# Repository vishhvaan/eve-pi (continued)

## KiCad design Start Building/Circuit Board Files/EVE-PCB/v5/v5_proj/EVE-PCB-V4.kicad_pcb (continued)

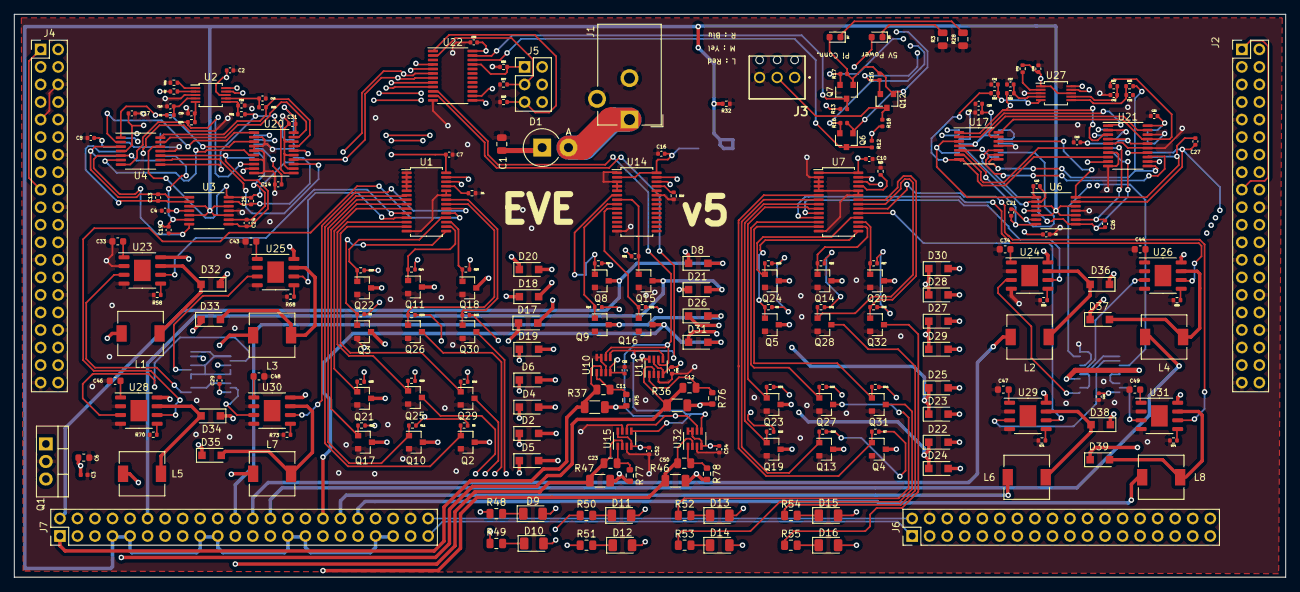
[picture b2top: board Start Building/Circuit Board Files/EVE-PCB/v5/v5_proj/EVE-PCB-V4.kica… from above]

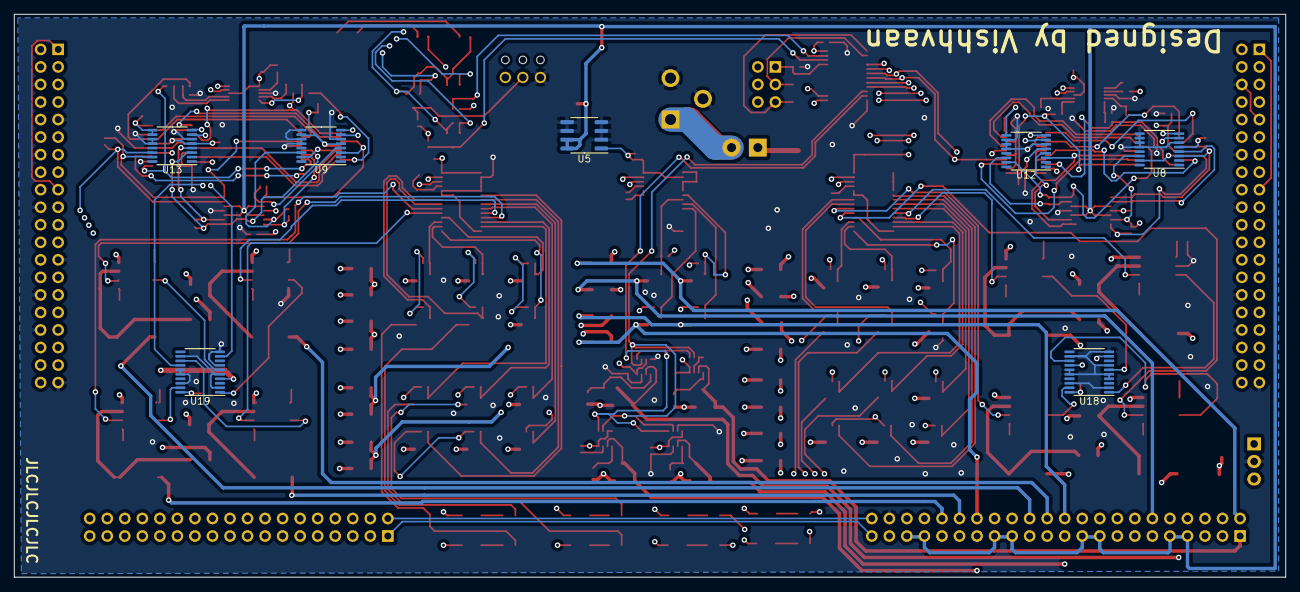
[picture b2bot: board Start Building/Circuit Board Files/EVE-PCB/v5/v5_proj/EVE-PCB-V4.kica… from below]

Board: 4 copper layers, 184.2 x 81.5 mm, 248 parts (7 on the bottom side), 193 nets.

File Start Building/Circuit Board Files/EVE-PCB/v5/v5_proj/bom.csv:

Comment,Designator,Footprint,LCSC
"10μF","C1","Capacitor_SMD:C_0805_2012Metric","C15850"
"1μF","C11,C12,C23,C50","Capacitor_SMD:C_0805_2012Metric","C28323"
"10pF","C13,C19,C20,C21,C24,C25,C26,C27","Capacitor_SMD:C_0402_1005Metric","C32949"
"2.2μF","C33,C34,C43,C44,C46,C47,C48,C49","Capacitor_SMD:C_0603_1608Metric","C23630"
"0.1μF","C2,C3,C4,C5,C7,C8,C9,C10,C14,C15,C16,C17,C18,C22,C28,C29,C30,C31,C32,C35,C36,C37,C38,C39,C40,C41,C42,C45,C51,C52,C54","Capacitor_SMD:C_0402_1005Metric","C1525"
"1μF","C6","Capacitor_SMD:C_0603_1608Metric","C5673"
"MUR480ERLG","D1","Diode_THT:D_DO-201AE_P3.81mm_Vertical_AnodeUp",""
"19-217/GHC-YR1S2/3T","D3","LED_SMD:LED_0603_1608Metric","C72043"
"PMEG6010CEH","D2,D4,D5,D6,D8,D17,D18,D19,D20,D21,D22,D23,D24,D25,D26,D27,D28,D29,D30,D31,D32,D33,D34,D35,D36,D37,D38,D39","Diode_SMD:D_SOD-123F","C110797"
"19-213/Y2C-CQ2R2L/3T","D7","LED_SMD:LED_0603_1608Metric","C72038"
"11-21/BHC-AQ2S1M/2T","D9,D10,D11,D12,D13,D14,D15,D16","LED_SMD:LED_1206_3216Metric","C264323"
"PJ-102AH","J1","Connector_BarrelJack:BarrelJack_CUI_PJ-102AH_Horizontal",""
"2x20 Male Header","J2,J4","Connector_PinHeader_2.54mm:PinHeader_2x20_P2.54mm_Vertical",""
"1725669","J3","1725669andothers:1725669",""
"Conn_02x03_Odd_Even","J5","Connector_PinHeader_2.54mm:PinHeader_2x03_P2.54mm_Vertical",""
"Conn_02x18_Odd_Even","J6","Connector_PinHeader_2.54mm:PinHeader_2x18_P2.54mm_Vertical",""
"Conn_02x22_Odd_Even","J7","Connector_PinHeader_2.54mm:PinHeader_2x22_P2.54mm_Vertical",""
"680uH","L1,L2,L3,L4,L5,L6,L7,L8","Inductor_SMD:L_6.3x6.3_H3","C168101"
"UA7805CKCT","Q1","Package_TO_SOT_THT:TO-220-3_Vertical",""
"DMN6140LQ-7","Q2,Q3,Q4,Q5,Q6,Q7,Q8,Q9,Q10,Q11,Q12,Q13,Q14,Q15,Q16,Q17,Q18,Q19,Q20,Q21,Q22,Q23,Q24,Q25,Q26,Q27,Q28,Q29,Q30,Q31,Q32","Package_TO_SOT_SMD:SOT-23","C155271"
"330KΩ","R1,R61,R62,R63,R64,R65,R66,R67","Resistor_SMD:R_0402_1005Metric","C25778"
"4.7KΩ","R15,R18","Resistor_SMD:R_0402_1005Metric","C25900"
"10KΩ","R2,R4,R5,R6,R7,R8,R9,R10,R11,R12,R13,R14,R16,R17,R19,R20,R21,R22,R23,R24,R25,R26,R27,R29,R30,R31,R32,R33,R34,R35,R38,R39,R40,R41,R42,R43,R44,R45,R56,R57,R60,R72","Resistor_SMD:R_0402_1005Metric","C25744"
"80Ω","R28,R48,R49,R50,R51,R52,R53,R54,R55","Resistor_SMD:R_0805_2012Metric","C17833"
"169Ω","R3","Resistor_SMD:R_0805_2012Metric","C17489"
"2.15Ω","R36,R37,R46,R47","Resistor_SMD:R_1206_3216Metric","C247507"
"20KΩ","R58,R59,R68,R69,R70,R71,R73,R74","Resistor_SMD:R_0402_1005Metric","C25765"
"750KΩ","R75,R76,R77,R78","Resistor_SMD:R_0603_1608Metric","C23240"
"PCA9685PW","U1,U7,U14","Package_SO:TSSOP-28_4.4x9.7mm_P0.65mm","C92206"
"INA219AxDCN","U10,U11,U15,U32","Package_TO_SOT_SMD:SOT-23-8","C87469"
"AD5254 - 50K","U18,U19,U20,U21","Package_SO:TSSOP-20_4.4x6.5mm_P0.65mm",""
"TCA9548APWR","U22","Package_SO:TSSOP-24_4.4x7.8mm_P0.65mm",""
"TPS92511DDAR","U23,U24,U25,U26,U28,U29,U30,U31","Package_SO:HSOP-8-1EP_3.9x4.9mm_P1.27mm_EP2.41x3.1mm","C206179"
"ADS1115IDGSR","U2,U27","Package_SO:MSOP-10_3x3mm_P0.5mm","C37593"
"TLV4314IPWR","U3,U4,U6,U17","Package_SO:TSSOP-14_4.4x5mm_P0.65mm","C106874"
"MCP1501-10E/SN","U5","Package_SO:SOIC-8_3.9x4.9mm_P1.27mm",""
"AD5242","U8,U9,U12,U13","Package_SO:TSSOP-16_4.4x5mm_P0.65mm",""

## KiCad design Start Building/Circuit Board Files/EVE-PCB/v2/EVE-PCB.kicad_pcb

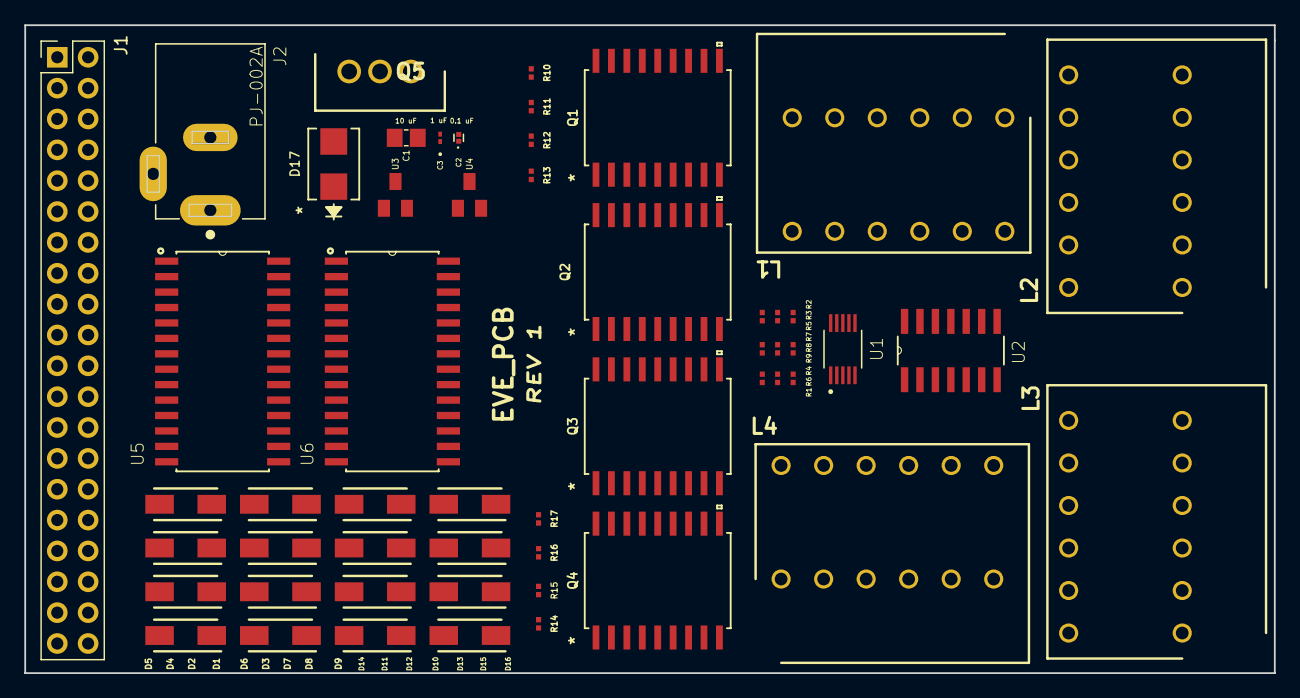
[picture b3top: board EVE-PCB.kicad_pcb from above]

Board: 2 copper layers, 102.9 x 53.3 mm, 54 parts (0 on the bottom side), 70 nets, no tracks yet.

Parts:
C1: 10 uF; CAPC2012X135N
C2: 0.1 uF; CAPC0603X39N
C3: 1 uF; GRM033R71E102KA01D
D1, D2, D3, D4, D5, D6, D7, D8, D9, D10, D11, D12, D13, D14, D15, D16: BAT43; B160-13-F
D17: S1KB; S1KB-13-F
J1: Raspberry_Pi_2_3; PinHeader_2x20_P2.54mm_Vertical
J2: PJ-002A; CUI_PJ-002A
L1, L2, L3, L4: SHDR12W60P935X350_2X6_2250X1800X2420P; 1841539
Q1, Q2, Q3, Q4: DW18; ULN2803ADWR
Q5: TO254P465X1016X1883-3P; UA7805CKCT
R1, R2, R3, R4: 1M; RC0201FR-071ML
R5, R6, R7, R8, R9: 10K; RC0201FR-0710KL
R10, R12, R14, R16: 130; RC0201FR-07130RL
R11, R13, R15, R17: 400; RC0201FR-07402RL
U1: ADS1015IDGSR; SOP50P490X110-10N
U2: LM324DR; SOIC127P600X175-14N
U3, U4: BSN20BKR; BSN20_215
U5, U6: MCP23017T-E_SO; SOIC127P1030X265-28N

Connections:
+3V3: J1.1, J1.17, R5.1, R9.1, U3.1, U4.1
+5V: C2.1, C3.1, Q5.3, R6.2, R7.1, R8.2, U1.8, U2.4, U5.9, U5.18, U6.9, U6.18
+12V: C1.1, D1.1, D2.1, D3.1, D4.1, D5.1, D6.1, D7.1, D8.1, D9.1, D10.1, D11.1, D12.1, D13.1, D14.1, D15.1, D16.1, D17.1, L1.7, L1.8, L1.9, L1.10, L1.11, L2.7, L2.8, L2.9, L2.10, L2.11, L3.7, L3.8, L3.9, L3.10, L3.11, L4.7, L4.8, L4.9, L4.10, L4.11, Q1.10, Q2.10, Q3.10, Q4.10, Q5.1
/AIN0: R1.1, U1.4, U2.1
/AIN1: R2.1, U1.5, U2.7
/AIN2: R3.1, U1.6, U2.8
/AIN3: R4.1, U1.7, U2.14
/DAC1/A_DRUGS1: D1.2, L1.1, Q1.18
/DAC1/A_DRUGS2: D5.2, L2.1, Q2.18
/DAC1/A_FAN1: Q1.14, R11.1
/DAC1/A_FAN2: Q2.14, R13.1
/DAC1/A_LED1: Q1.15, R10.1
/DAC1/A_LED2: Q2.15, R12.1
/DAC1/A_MEDIA1: D2.2, L1.2, Q1.17
/DAC1/A_MEDIA2: D6.2, L2.2, Q2.17
/DAC1/A_SFAN1: D4.2, L1.4, Q1.13, R11.2
/DAC1/A_SFAN2: D8.2, L2.4, Q2.13, R13.2
/DAC1/A_WASTE1: D3.2, L1.3, Q1.16
/DAC1/A_WASTE2: D7.2, L2.3, Q2.16
/DAC1/D_DRUGS1: Q1.1, U5.21
/DAC1/D_DRUGS2: Q2.1, U5.1
/DAC1/D_FAN1: Q1.5, U5.25
/DAC1/D_FAN2: Q2.5, U5.5
/DAC1/D_LED1: Q1.4, U5.24
/DAC1/D_LED2: Q2.4, U5.4
/DAC1/D_MEDIA1: Q1.2, U5.22
/DAC1/D_MEDIA2: Q2.2, U5.2
/DAC1/D_SFAN1: Q1.6, U5.26
/DAC1/D_SFAN2: Q2.6, U5.6
/DAC1/D_WASTE1: Q1.3, U5.23
/DAC1/D_WASTE2: Q2.3, U5.3
/DAC1/LED1_NEG: L1.5, R10.2
/DAC1/LED2_NEG: L2.5, R12.2
/DAC2/A_DRUGS3: D9.2, L3.1, Q3.18
/DAC2/A_DRUGS4: D13.2, L4.1, Q4.18
/DAC2/A_FAN3: Q3.14, R15.1
/DAC2/A_FAN4: Q4.14, R17.1
/DAC2/A_LED3: Q3.15, R14.1
/DAC2/A_LED4: Q4.15, R16.1
/DAC2/A_MEDIA3: D10.2, L3.2, Q3.17
/DAC2/A_MEDIA4: D14.2, L4.2, Q4.17
/DAC2/A_SFAN3: D12.2, L3.4, Q3.13, R15.2
/DAC2/A_SFAN4: D16.2, L4.4, Q4.13, R17.2
/DAC2/A_WASTE3: D11.2, L3.3, Q3.16
/DAC2/A_WASTE4: D15.2, L4.3, Q4.16
/DAC2/D_DRUGS3: Q3.1, U6.21
/DAC2/D_DRUGS4: Q4.1, U6.1
/DAC2/D_FAN3: Q3.5, U6.25
/DAC2/D_FAN4: Q4.5, U6.5
/DAC2/D_LED3: Q3.4, U6.24
/DAC2/D_LED4: Q4.4, U6.4
/DAC2/D_MEDIA3: Q3.2, U6.22
/DAC2/D_MEDIA4: Q4.2, U6.2
/DAC2/D_SFAN3: Q3.6, U6.26
/DAC2/D_SFAN4: Q4.6, U6.6
/DAC2/D_WASTE3: Q3.3, U6.23
/DAC2/D_WASTE4: Q4.3, U6.3
/DAC2/LED3_NEG: L3.5, R14.2
/DAC2/LED4_NEG: L4.5, R16.2
/PD1_NEG: L1.6, R1.2, U2.2
/PD2_NEG: L2.6, R2.2, U2.6
/PD3_NEG: L3.6, R3.2, U2.9
/PD4_NEG: L4.6, R4.2, U2.13
/SCL: R6.1, U1.10, U3.3, U5.12, U6.12
/SCL-3.3: J1.5, R5.2, U3.2
/SDA: R8.1, U1.9, U4.3, U5.13, U6.13
/SDA-3.3: J1.3, R9.2, U4.2
GND: C1.2, C2.2, C3.2, J1.6, J1.9, J1.14, J1.20, J1.25, J1.30, J1.34, J1.39, J2.2, J2.3, L1.12, L2.12, L3.12, L4.12, Q1.9, Q2.9, Q3.9, Q4.9, Q5.2, U1.1, U1.3, U2.3, U2.5, U2.10, U2.11, U2.12, U5.10, U5.15, U5.16, U5.17, U6.10, U6.15, U6.16, U6.17
unnamed: D17.2, J2.1
unnamed: R7.2, U1.2

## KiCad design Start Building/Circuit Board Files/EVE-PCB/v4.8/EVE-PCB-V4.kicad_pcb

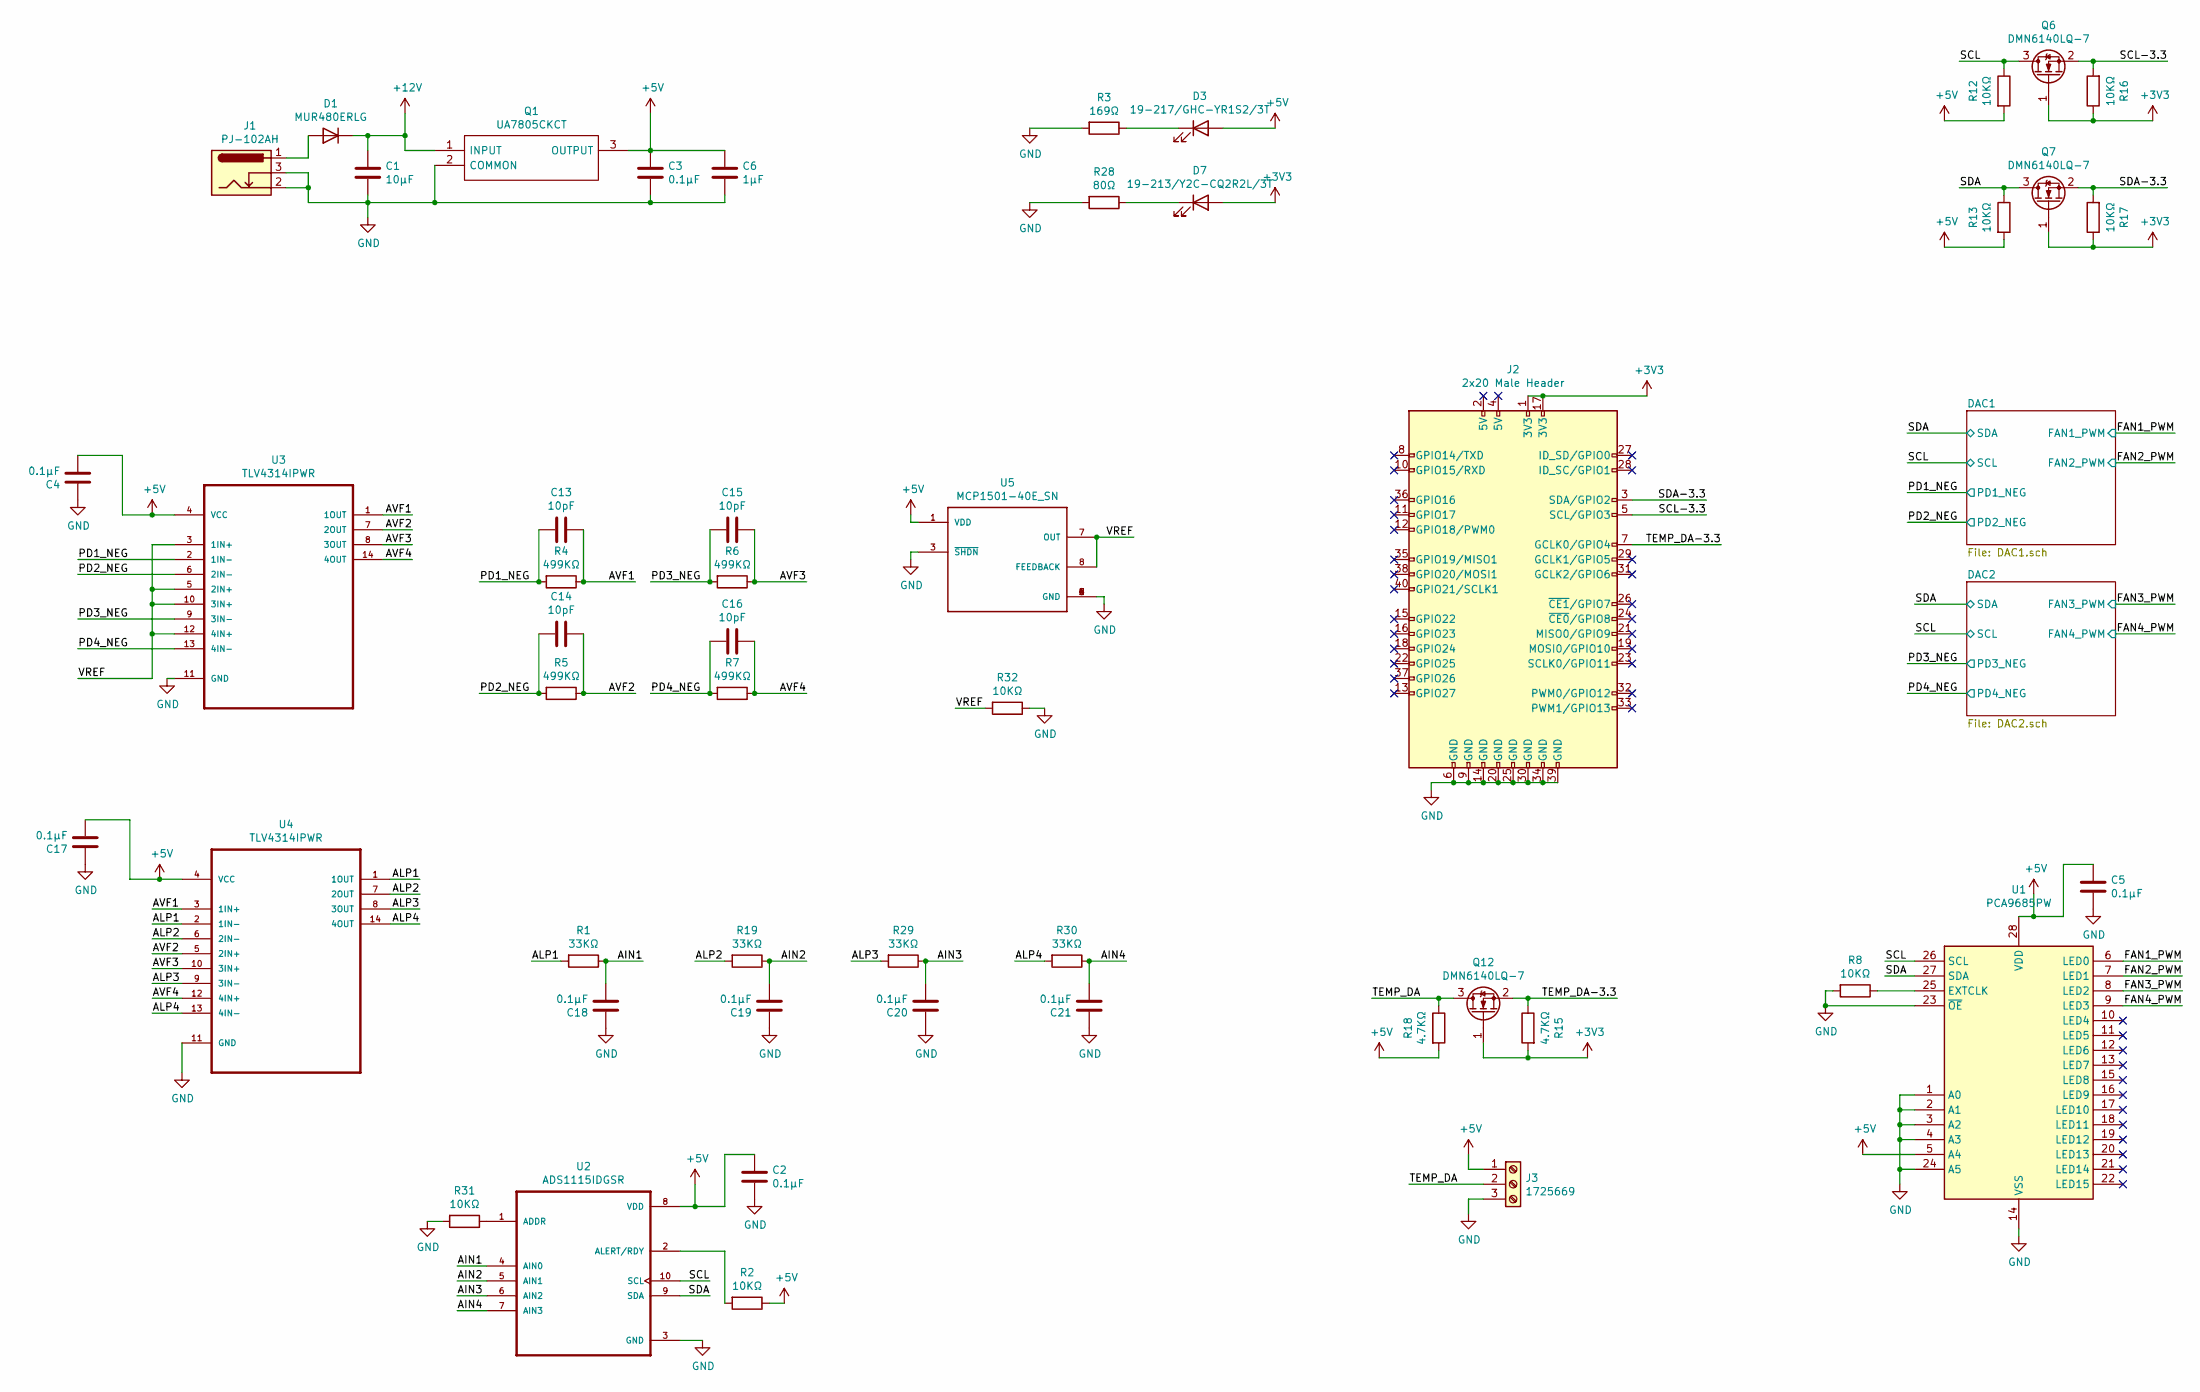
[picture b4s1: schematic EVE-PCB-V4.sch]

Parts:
C1: 10μF; C_0805_2012Metric; LCSC C15850
C2, C3, C4, C5, C17, C18, C19, C20, C21: 0.1μF; C_0402_1005Metric; LCSC C1525
C6: 1μF; C_0603_1608Metric; LCSC C5673
C13, C14, C15, C16: 10pF; C_0402_1005Metric; LCSC C32949
D1: MUR480ERLG; D_DO-201AE_P3.81mm_Vertical_AnodeUp
D3: 19-217/GHC-YR1S2/3T; LED_0603_1608Metric; LCSC C72043
D7: 19-213/Y2C-CQ2R2L/3T; LED_0603_1608Metric; LCSC C72038
J1: PJ-102AH; BarrelJack_CUI_PJ-102AH_Horizontal
J2: 2x20 Male Header; PinHeader_2x20_P2.54mm_Vertical
J3: 1725669
Q1: UA7805CKCT; TO-220-3_Vertical; Mouser Part Number 595-UA7805CKCT
Q6, Q7, Q12: DMN6140LQ-7; SOT-23; LCSC C155271
R1, R19, R29, R30: 33KΩ; R_0402_1005Metric; LCSC C25779
R2, R8, R12, R13, R16, R17, R31, R32: 10KΩ; R_0402_1005Metric; LCSC C25744
R3: 169Ω; R_0805_2012Metric; LCSC C17489
R4, R5, R6, R7: 499KΩ; R_0402_1005Metric; LCSC C25793
R15, R18: 4.7KΩ; R_0402_1005Metric; LCSC C25900
R28: 80Ω; R_0805_2012Metric; LCSC C17833
U1: PCA9685PW; TSSOP-28_4.4x9.7mm_P0.65mm; LCSC C92206
U2: ADS1115IDGSR; MSOP-10_3x3mm_P0.5mm; LCSC C37593
U3, U4: TLV4314IPWR; TSSOP-14_4.4x5mm_P0.65mm; LCSC C106874
U5: MCP1501-40E_SN; SOIC-8_3.9x4.9mm_P1.27mm

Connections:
+3V3: D7.2 (A), J2.1 (3V3), J2.17 (3V3), Q6.1 (G), Q7.1 (G), Q12.1 (G), R15.2, R16.1, R17.1
+5V: C2.1, C3.1, C4.2, C5.1, C6.1, C17.2, D3.2 (A), J3.1, Q1.3 (OUTPUT), R2.1, R12.2, R13.2, R18.2, U1.5 (A4), U1.28 (VDD), U2.8 (VDD), U3.4 (VCC), U4.4 (VCC), U5.1 (VDD); also elsewhere on the board
+12V: C1.1, D1.1 (K), Q1.1 (INPUT); also elsewhere on the board
/AIN1: C18.2, R1.1, U2.4 (AIN0)
/AIN2: C19.2, R19.1, U2.5 (AIN1)
/AIN3: C20.2, R29.1, U2.6 (AIN2)
/AIN4: C21.2, R30.1, U2.7 (AIN3)
/ALP1: R1.2, U4.1 (1OUT), U4.2 (1IN-)
/ALP2: R19.2, U4.6 (2IN-), U4.7 (2OUT)
/ALP3: R29.2, U4.8 (3OUT), U4.9 (3IN-)
/ALP4: R30.2, U4.13 (4IN-), U4.14 (4OUT)
/AVF1: C13.1, R4.1, U3.1 (1OUT), U4.3 (1IN+)
/AVF2: C14.1, R5.1, U3.7 (2OUT), U4.5 (2IN+)
/AVF3: C15.1, R6.1, U3.8 (3OUT), U4.10 (3IN+)
/AVF4: C16.1, R7.1, U3.14 (4OUT), U4.12 (4IN+)
/FAN1_PWM: U1.6 (LED0); also elsewhere on the board
/FAN2_PWM: U1.7 (LED1); also elsewhere on the board
/FAN3_PWM: U1.8 (LED2); also elsewhere on the board
/FAN4_PWM: U1.9 (LED3); also elsewhere on the board
/PD1_NEG: C13.2, R4.2, U3.2 (1IN-); also elsewhere on the board
/PD2_NEG: C14.2, R5.2, U3.6 (2IN-); also elsewhere on the board
/PD3_NEG: C15.2, R6.2, U3.9 (3IN-); also elsewhere on the board
/PD4_NEG: C16.2, R7.2, U3.13 (4IN-); also elsewhere on the board
/SCL: Q6.3 (D), R12.1, U1.26 (SCL), U2.10 (SCL); also elsewhere on the board
/SCL-3.3: J2.5 (SCL/GPIO3), Q6.2 (S), R16.2
/SDA: Q7.3 (D), R13.1, U1.27 (SDA), U2.9 (SDA); also elsewhere on the board
/SDA-3.3: J2.3 (SDA/GPIO2), Q7.2 (S), R17.2
/TEMP_DA: J3.2, Q12.3 (D), R18.1
/TEMP_DA-3.3: J2.7 (GCLK0/GPIO4), Q12.2 (S), R15.1
/VREF: R32.2, U3.3 (1IN+), U3.5 (2IN+), U3.10 (3IN+), U3.12 (4IN+), U5.7 (OUT), U5.8 (FEEDBACK)
GND: C1.2, C2.2, C3.2, C4.1, C5.2, C6.2, C17.1, C18.1, C19.1, C20.1, C21.1, J1.2, J1.3, J2.6 (GND), J2.9 (GND), J2.14 (GND), J2.20 (GND), J2.25 (GND), J2.30 (GND), J2.34 (GND), J2.39 (GND), J3.3, Q1.2 (COMMON), R3.2, R8.2, R28.2, R31.2, R32.1, U1.1 (A0), U1.2 (A1), U1.3 (A2), U1.4 (A3), U1.14 (VSS), U1.23 (~OE), U1.24 (A5), U2.3 (GND), U3.11 (GND), U4.11 (GND), U5.2 (GND), U5.3 (~SHDN~), U5.4 (GND), U5.5 (GND), U5.6 (GND); also elsewhere on the board
unnamed: D1.2 (A), J1.1
unnamed: D3.1 (K), R3.1
unnamed: D7.1 (K), R28.1
unnamed: R2.2, U2.2 (ALERT/RDY)
unnamed: R8.1, U1.25 (EXTCLK)
unnamed: R31.1, U2.1 (ADDR)

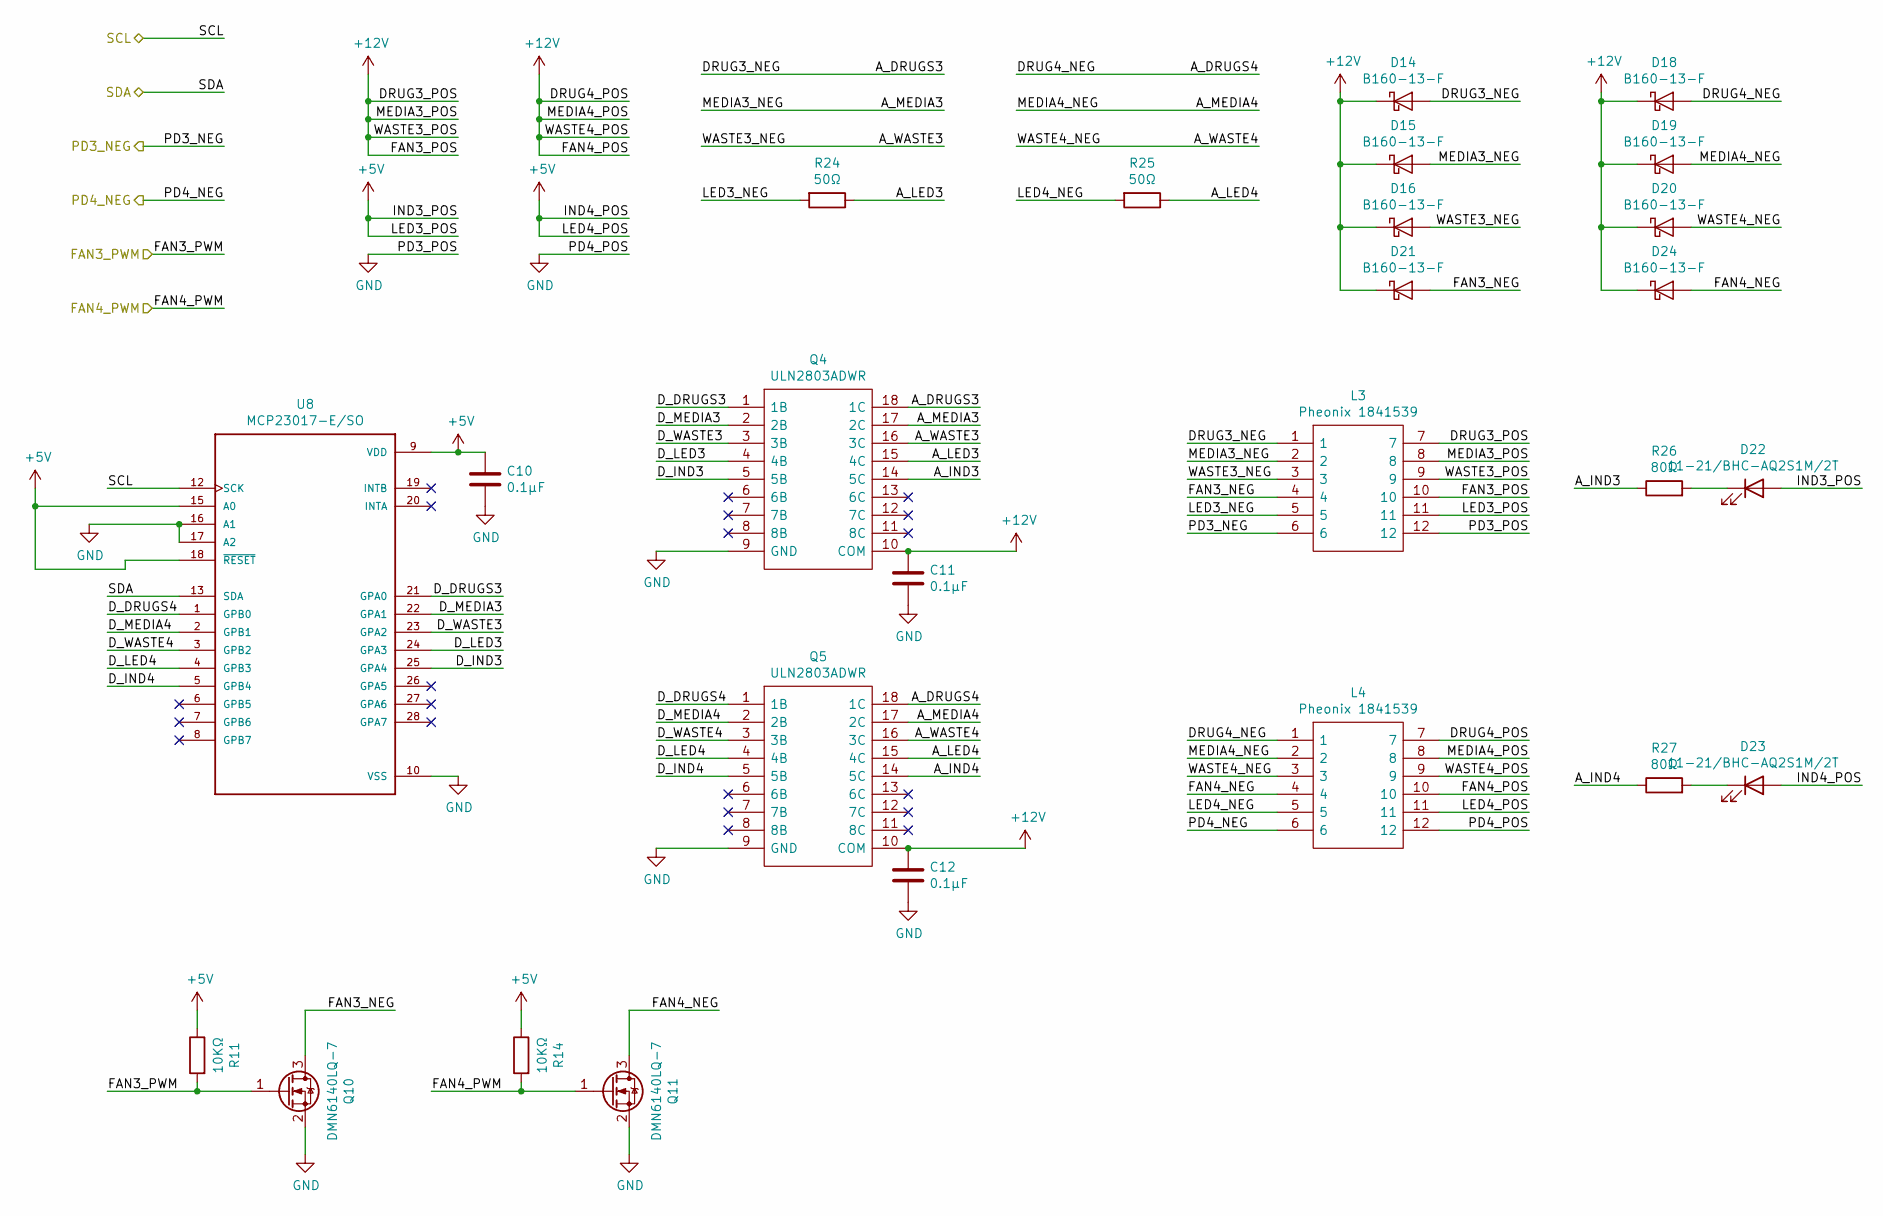
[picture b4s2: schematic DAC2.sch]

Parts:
C10, C11, C12: 0.1μF; C_0402_1005Metric; LCSC C1525
D14, D15, D16, D18, D19, D20, D21, D24: B160-13-F; D_SMA; LCSC C24784
D22, D23: 11-21/BHC-AQ2S1M/2T; LED_1206_3216Metric; LCSC C264323
L3, L4: Pheonix 1841539; 1841539; Mouser Part Number 651-1841539
Q4, Q5: ULN2803ADWR; SOIC-18W_7.5x11.6mm_P1.27mm; Mouser Part Number 595-ULN2803ADWR
Q10, Q11: DMN6140LQ-7; SOT-23; LCSC C155271
R11, R14: 10KΩ; R_0402_1005Metric; LCSC C25744
R24, R25: 50Ω; R_2512_6332Metric; LCSC C25487
R26, R27: 80Ω; R_0805_2012Metric; LCSC C17833
U8: MCP23017-E/SO; SOIC-28W_7.5x17.9mm_P1.27mm; LCSC C47023

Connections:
+5V: C10.1, D22.2 (A), D23.2 (A), L3.11, L4.11, R11.1, R14.1, U8.9 (VDD), U8.15 (A0), U8.18 (~RESET~); also elsewhere on the board
+12V: C11.1, C12.1, D14.1 (K), D15.1 (K), D16.1 (K), D18.1 (K), D19.1 (K), D20.1 (K), D21.1 (K), D24.1 (K), L3.7, L3.8, L3.9, L3.10, L4.7, L4.8, L4.9, L4.10, Q4.10 (COM), Q5.10 (COM); also elsewhere on the board
/DAC2/A_DRUGS3: D14.2 (A), L3.1, Q4.18 (1C)
/DAC2/A_DRUGS4: D18.2 (A), L4.1, Q5.18 (1C)
/DAC2/A_IND3: Q4.14 (5C), R26.1
/DAC2/A_IND4: Q5.14 (5C), R27.1
/DAC2/A_LED3: Q4.15 (4C), R24.1
/DAC2/A_LED4: Q5.15 (4C), R25.1
/DAC2/A_MEDIA3: D15.2 (A), L3.2, Q4.17 (2C)
/DAC2/A_MEDIA4: D19.2 (A), L4.2, Q5.17 (2C)
/DAC2/A_WASTE3: D16.2 (A), L3.3, Q4.16 (3C)
/DAC2/A_WASTE4: D20.2 (A), L4.3, Q5.16 (3C)
/DAC2/D_DRUGS3: Q4.1 (1B), U8.21 (GPA0)
/DAC2/D_DRUGS4: Q5.1 (1B), U8.1 (GPB0)
/DAC2/D_IND3: Q4.5 (5B), U8.25 (GPA4)
/DAC2/D_IND4: Q5.5 (5B), U8.5 (GPB4)
/DAC2/D_LED3: Q4.4 (4B), U8.24 (GPA3)
/DAC2/D_LED4: Q5.4 (4B), U8.4 (GPB3)
/DAC2/D_MEDIA3: Q4.2 (2B), U8.22 (GPA1)
/DAC2/D_MEDIA4: Q5.2 (2B), U8.2 (GPB1)
/DAC2/D_WASTE3: Q4.3 (3B), U8.23 (GPA2)
/DAC2/D_WASTE4: Q5.3 (3B), U8.3 (GPB2)
/DAC2/FAN3_NEG: D21.2 (A), L3.4, Q10.3 (D)
/DAC2/FAN4_NEG: D24.2 (A), L4.4, Q11.3 (D)
/DAC2/LED3_NEG: L3.5, R24.2
/DAC2/LED4_NEG: L4.5, R25.2
/FAN3_PWM: Q10.1 (G), R11.2; also elsewhere on the board
/FAN4_PWM: Q11.1 (G), R14.2; also elsewhere on the board
/PD3_NEG: L3.6; also elsewhere on the board
/PD4_NEG: L4.6; also elsewhere on the board
/SCL: U8.12 (SCK); also elsewhere on the board
/SDA: U8.13 (SDA); also elsewhere on the board
GND: C10.2, C11.2, C12.2, L3.12, L4.12, Q4.9 (GND), Q5.9 (GND), Q10.2 (S), Q11.2 (S), U8.10 (VSS), U8.16 (A1), U8.17 (A2); also elsewhere on the board
unnamed: D22.1 (K), R26.2
unnamed: D23.1 (K), R27.2

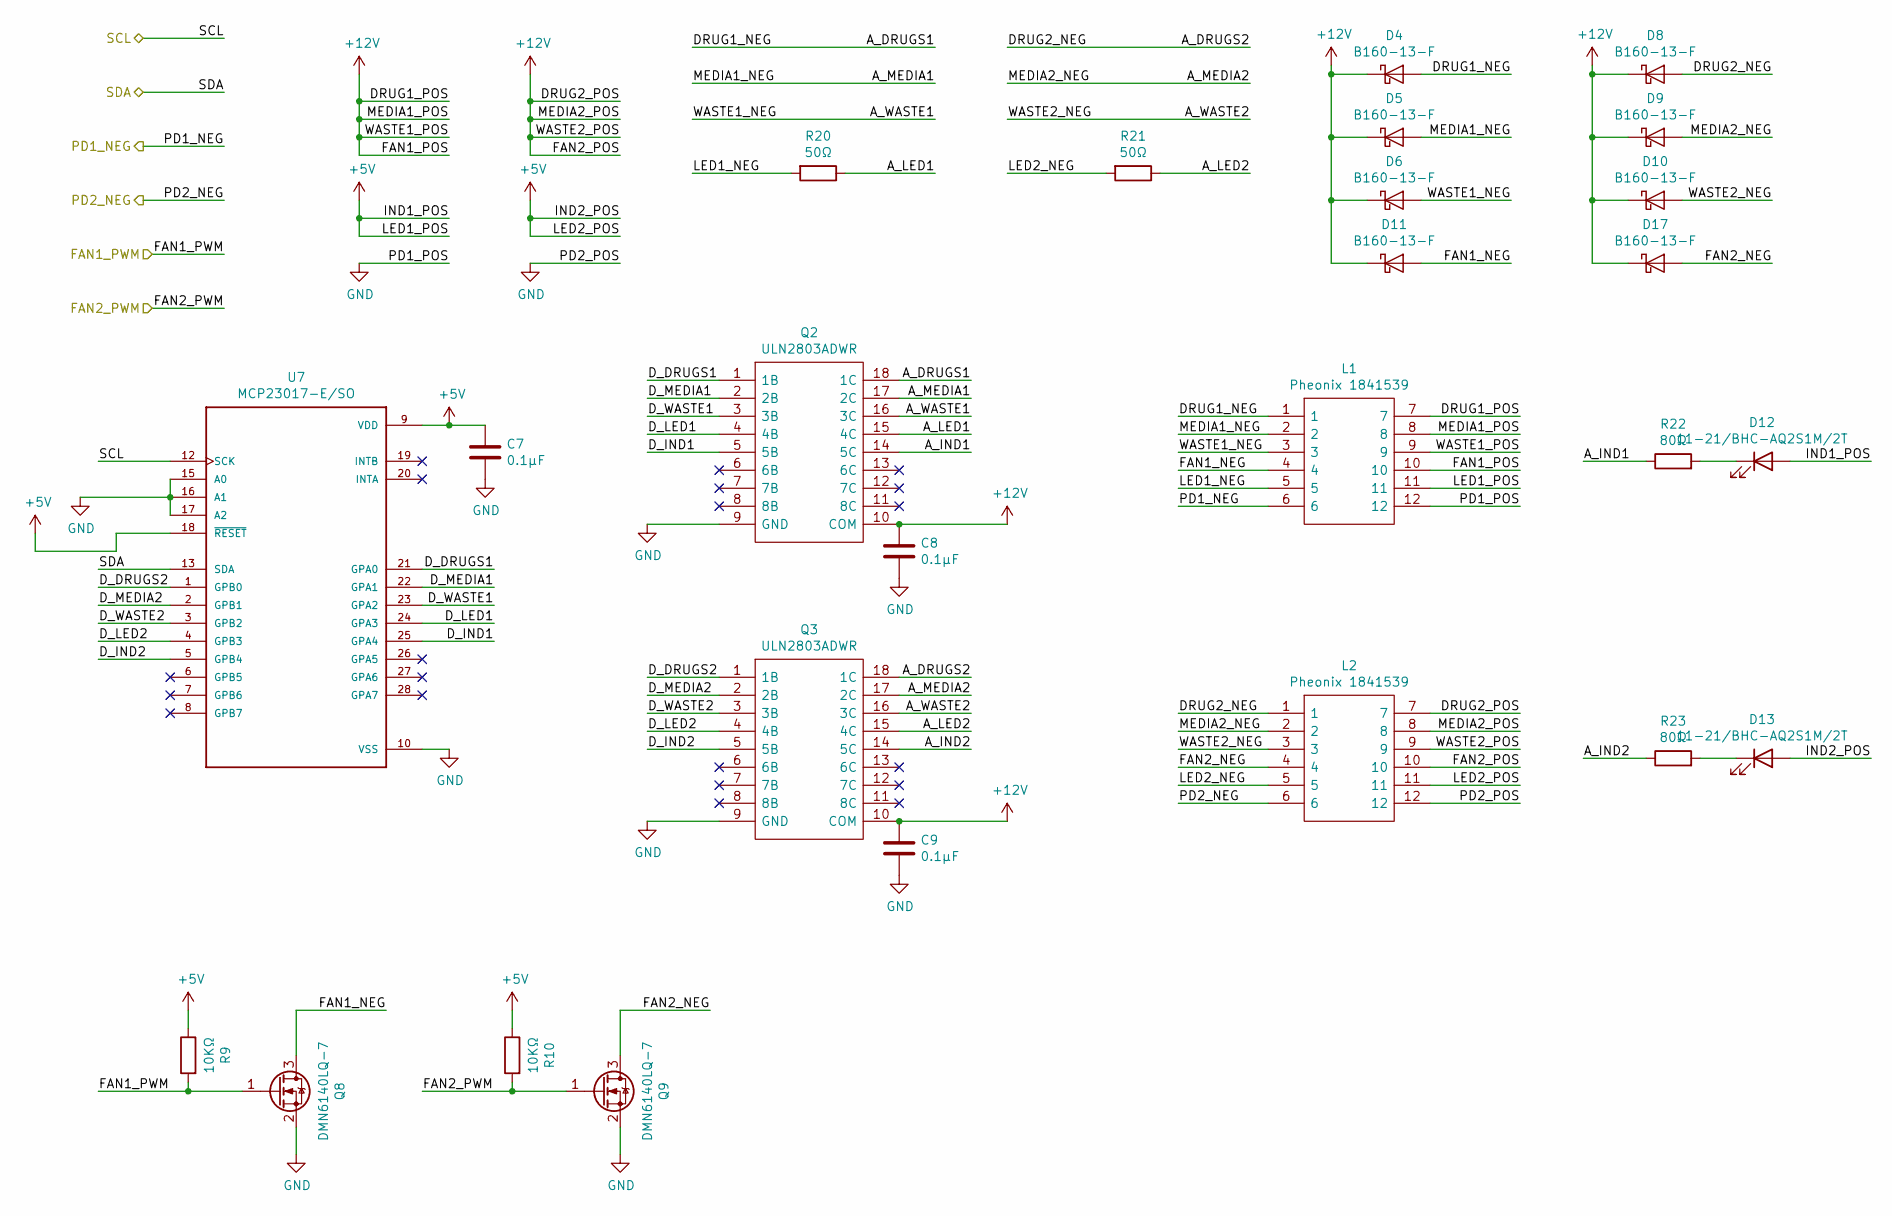
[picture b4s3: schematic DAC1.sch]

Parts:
C7, C8, C9: 0.1μF; C_0402_1005Metric; LCSC C1525
D4, D5, D6, D8, D9, D10, D11, D17: B160-13-F; D_SMA; LCSC C24784
D12, D13: 11-21/BHC-AQ2S1M/2T; LED_1206_3216Metric; LCSC C264323
L1, L2: Pheonix 1841539; 1841539; Mouser Part Number 651-1841539
Q2, Q3: ULN2803ADWR; SOIC-18W_7.5x11.6mm_P1.27mm; Mouser Part Number 595-ULN2803ADWR
Q8, Q9: DMN6140LQ-7; SOT-23; LCSC C155271
R9, R10: 10KΩ; R_0402_1005Metric; LCSC C25744
R20, R21: 50Ω; R_2512_6332Metric; LCSC C25487
R22, R23: 80Ω; R_0805_2012Metric; LCSC C17833
U7: MCP23017-E/SO; SOIC-28W_7.5x17.9mm_P1.27mm; LCSC C47023

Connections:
+5V: C7.1, D12.2 (A), D13.2 (A), L1.11, L2.11, R9.1, R10.1, U7.9 (VDD), U7.18 (~RESET~); also elsewhere on the board
+12V: C8.1, C9.1, D4.1 (K), D5.1 (K), D6.1 (K), D8.1 (K), D9.1 (K), D10.1 (K), D11.1 (K), D17.1 (K), L1.7, L1.8, L1.9, L1.10, L2.7, L2.8, L2.9, L2.10, Q2.10 (COM), Q3.10 (COM); also elsewhere on the board
/DAC1/A_DRUGS1: D4.2 (A), L1.1, Q2.18 (1C)
/DAC1/A_DRUGS2: D8.2 (A), L2.1, Q3.18 (1C)
/DAC1/A_IND1: Q2.14 (5C), R22.1
/DAC1/A_IND2: Q3.14 (5C), R23.1
/DAC1/A_LED1: Q2.15 (4C), R20.1
/DAC1/A_LED2: Q3.15 (4C), R21.1
/DAC1/A_MEDIA1: D5.2 (A), L1.2, Q2.17 (2C)
/DAC1/A_MEDIA2: D9.2 (A), L2.2, Q3.17 (2C)
/DAC1/A_WASTE1: D6.2 (A), L1.3, Q2.16 (3C)
/DAC1/A_WASTE2: D10.2 (A), L2.3, Q3.16 (3C)
/DAC1/D_DRUGS1: Q2.1 (1B), U7.21 (GPA0)
/DAC1/D_DRUGS2: Q3.1 (1B), U7.1 (GPB0)
/DAC1/D_IND1: Q2.5 (5B), U7.25 (GPA4)
/DAC1/D_IND2: Q3.5 (5B), U7.5 (GPB4)
/DAC1/D_LED1: Q2.4 (4B), U7.24 (GPA3)
/DAC1/D_LED2: Q3.4 (4B), U7.4 (GPB3)
/DAC1/D_MEDIA1: Q2.2 (2B), U7.22 (GPA1)
/DAC1/D_MEDIA2: Q3.2 (2B), U7.2 (GPB1)
/DAC1/D_WASTE1: Q2.3 (3B), U7.23 (GPA2)
/DAC1/D_WASTE2: Q3.3 (3B), U7.3 (GPB2)
/DAC1/FAN1_NEG: D11.2 (A), L1.4, Q8.3 (D)
/DAC1/FAN2_NEG: D17.2 (A), L2.4, Q9.3 (D)
/DAC1/LED1_NEG: L1.5, R20.2
/DAC1/LED2_NEG: L2.5, R21.2
/FAN1_PWM: Q8.1 (G), R9.2; also elsewhere on the board
/FAN2_PWM: Q9.1 (G), R10.2; also elsewhere on the board
/PD1_NEG: L1.6; also elsewhere on the board
/PD2_NEG: L2.6; also elsewhere on the board
/SCL: U7.12 (SCK); also elsewhere on the board
/SDA: U7.13 (SDA); also elsewhere on the board
GND: C7.2, C8.2, C9.2, L1.12, L2.12, Q2.9 (GND), Q3.9 (GND), Q8.2 (S), Q9.2 (S), U7.10 (VSS), U7.15 (A0), U7.16 (A1), U7.17 (A2); also elsewhere on the board
unnamed: D12.1 (K), R22.2
unnamed: D13.1 (K), R23.2

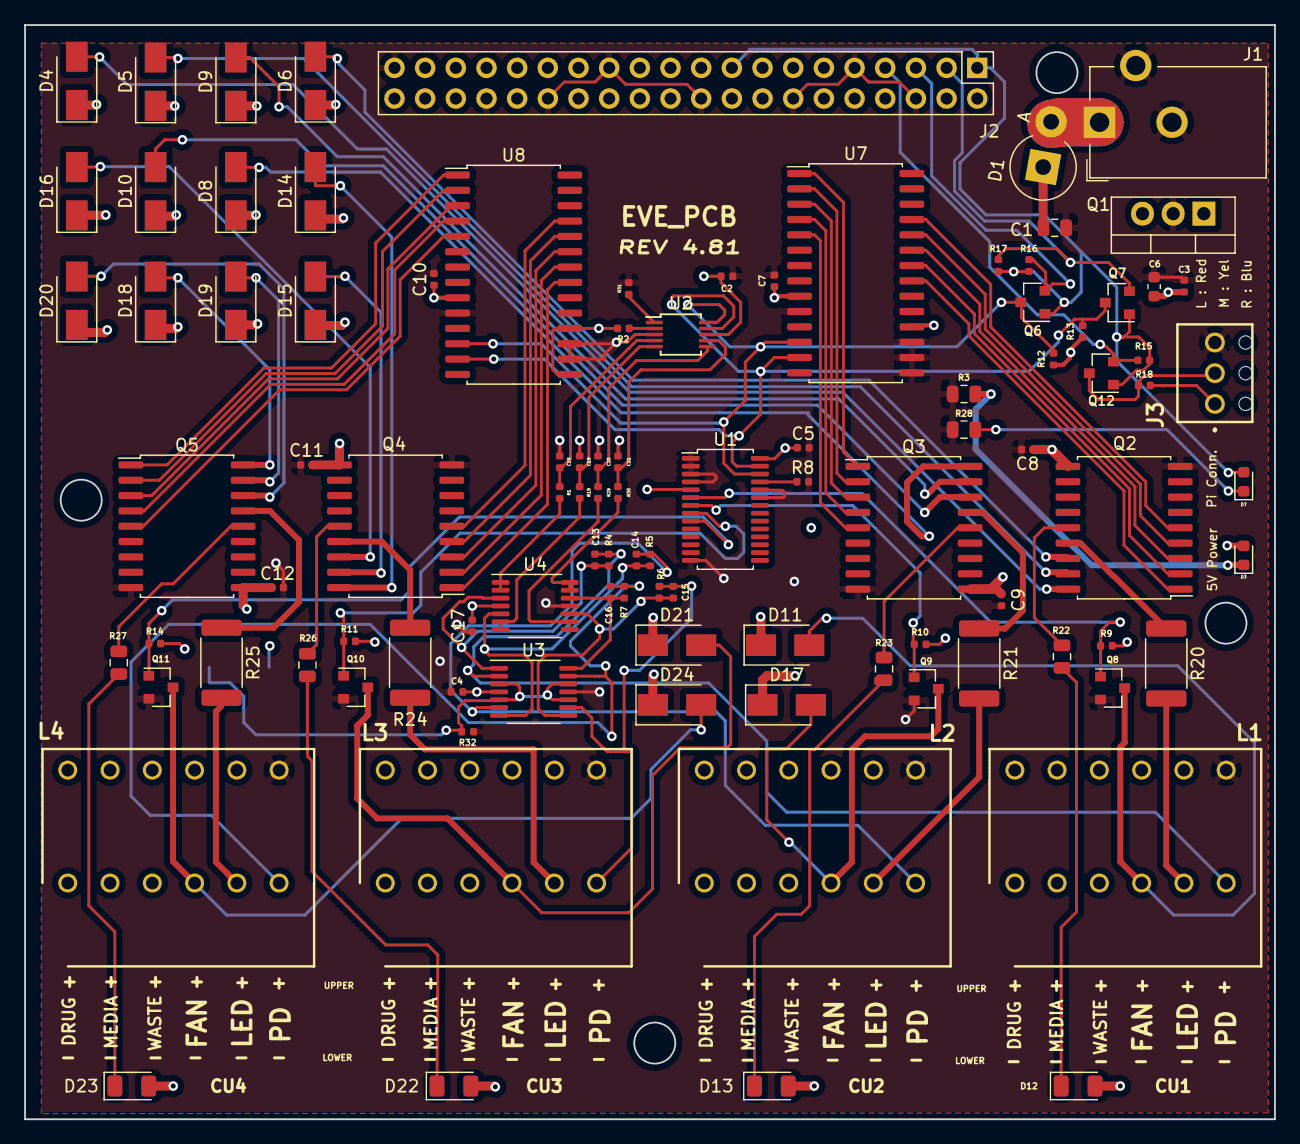
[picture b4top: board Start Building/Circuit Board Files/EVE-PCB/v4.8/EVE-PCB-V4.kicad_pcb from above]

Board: 4 copper layers, 103.5 x 90.6 mm, 102 parts (1 on the bottom side), 89 nets.

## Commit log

2019-04-17 Clean up
2019-04-17 steve added
2019-04-18 file clean up
2019-04-19 No Keys
2019-04-24 queue system
2019-05-03 Scaling OD
2019-05-20 script in tmux
2019-05-20 cleanup
2019-06-14 service files
2019-06-17 Create LICENSE
2019-06-17 Update local repo
2019-06-18 steve update
2019-06-19 added sample configuration file
2019-06-25 Dockerfiles
2019-06-25 Scaling Media Threshold
2019-07-10 Fix of MCP23017
2019-07-10 Another update for the MCP23017
2019-07-15 Updates to setup script
2019-07-18 Added temperature sensing
2019-07-19 Slack updates
2019-07-19 Temp Sensing Fixes
2019-07-19 Replace Multiplexer with hostname
2019-07-21 Slack API Bugfixes
2019-07-21 Disabled Slack Responder & Improve Slack API handling
2019-07-22 Save Locations added to config file
2019-07-24 Revert to Slack 1.3.2
2019-07-24 Setup script: Enforce Slackclient 1.3.2 and fix typo in webui service copy command
2019-07-26 Fix JSON Errors
2019-07-26 Added Modifiable Drug Concentrations and Drug Name
2019-08-04 Added Real-time toggleable combined growth curves of multiplex experiments
2019-08-05 Added 3D files
2019-08-06 Added Circuit Board files
2019-08-08 Added Parts List
2019-08-09 Organization
2019-08-19 Rename EVEs to CU
2019-09-10 Added other bioreactor modes. Calculation of dilution rate. Steamline control algorithm.
2019-09-16 Update Parts List
2019-09-21 Seperate flow rates
2019-12-05 add .gitignore for *.pyc files
2019-12-05 fixed small bugs
2020-04-20 PCB Updates
2020-05-22 PCB v4.5 and below
2020-05-22 Remove reboot from setup
2020-05-23 PCB v4.5 temp sensor PCB addition
2020-05-29 Updates to v4.5 and include support for ADS1115
2020-05-29 Improve fan control via webui and indicator light support
2020-06-10 v4.5 updates
2020-06-10 Prep webui update
2020-06-10 Squashed 'webui/' content from commit 42b7898
    git-subtree-dir: webui
    git-subtree-split: 42b789848fa4dff208a2286971deb569079b1e3c
2020-06-10 Script server customizations
2020-06-10 Remove unnecessary hostname configuration
2020-06-10 Add webui service file
2020-06-11 Update for terminology from config file
2020-06-11 Update configuration paramater definitions
2020-06-12 Update setup script with support for PWM chip and reboot prompt
2020-06-12 Update pumpsledoff.py to include optional indicator LEDs
2020-06-12 Remove testing code
2020-06-13 Add indicator light support to LED test script
2020-06-18 Bump PCB version to 4.81
    - Added buffer before ADC
    - Reduced photodiode amplification to limit saturation
    - Added optional 1V Vref to TIA
    - Added passive 50Hz low pass filter before ADC
2020-06-18 Remove hard path
2020-06-19 Update schematic pdf
2020-06-26 Bump PCB version to 4.81
    - Fixed voltages for fan and LED
2020-06-27 Update schematics
2020-07-01 Update setup instructions
2020-07-15 Updates to PCB 4.81
2020-07-16 Implement software low-pass filter for OD readings
2020-07-16 Fixes for software low-pass filter
2020-07-22 Update 3D Files
2020-07-27 Update setup script to install WebUI
2020-07-28 Bump PCB to version 4.82
    - Update schematic to use V_ref as PD positive terminal.
    - Update PCB to allow for this change.
2020-07-30 Update circuit schematic
2020-08-01 Rename schematic
2020-08-01 Revert fan percentage to float
2020-08-04 Update photodiode definitions
2020-09-27 Start PCB v5
2020-10-19 Finalize schematic
2020-10-19 Add manuscript folder
2020-10-30 Zip manuscript data
2020-11-20 Starting the wiring
2020-11-20 Add PCB image
2020-11-20 Add PCB and Holder image
2020-11-23 Major placment updates
2021-02-14 PCBv5 updates
2021-02-14 Squashed 'webui/' changes from 42b7898..9789e2d
    9789e2d #387 fixed broken test
    289a0ee #388 fixed empty element in the list if there is no script output
    37169b8 #387 allowed acceess to script status by admins
    d67f906 updated npm dependencies versions
    5ddcb59 Create FUNDING.yml
    3ff60dd #385 made "setAllParameterValues" atomic to avoid concurrent issues with updating parameters one by one. + improved forcedValues for obsolete values with proper validation error and automatic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
2021-03-29 PCBv5 redesign current sensing
2021-03-29 Squashed 'webui/' changes from 9789e2d..9ce26b3
    9ce26b3 #398 refactored same_arg_param/repeat_param/multiple_arguments option for consistency
    20a94e4 fixed vulnerable marked version
    2d1001f #418 updated base docker image to python 3.9
    c1d360b #283 added possibility to exclude files from server_file parameters
    b1bab1f #225 added editable_list type, where a user can either select value or type his own
    f083252 #417 fixed loading crypt module on windows (it's failing, even without being invoked)
2021-05-04 PCBv5 update some schematics
2021-05-04 Typo
2021-10-03 Updates to PCB v5
2021-11-07 Not needed line
2021-11-07 Switch to w1thermsensor library
2021-11-08 Catch w1thermsensor error
2021-11-10 Update README.md
    https://forum.kicad.info/t/warning-avoid-all-links-to-kicad-pcb-org-use-kicad-org/31521
